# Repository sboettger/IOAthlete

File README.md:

# IOAthlete
A fork of the Reaction Training Dummy of instructables
https://www.instructables.com/Reaction-Training-Dummy/

TODO: add symbols and footprints to the repository

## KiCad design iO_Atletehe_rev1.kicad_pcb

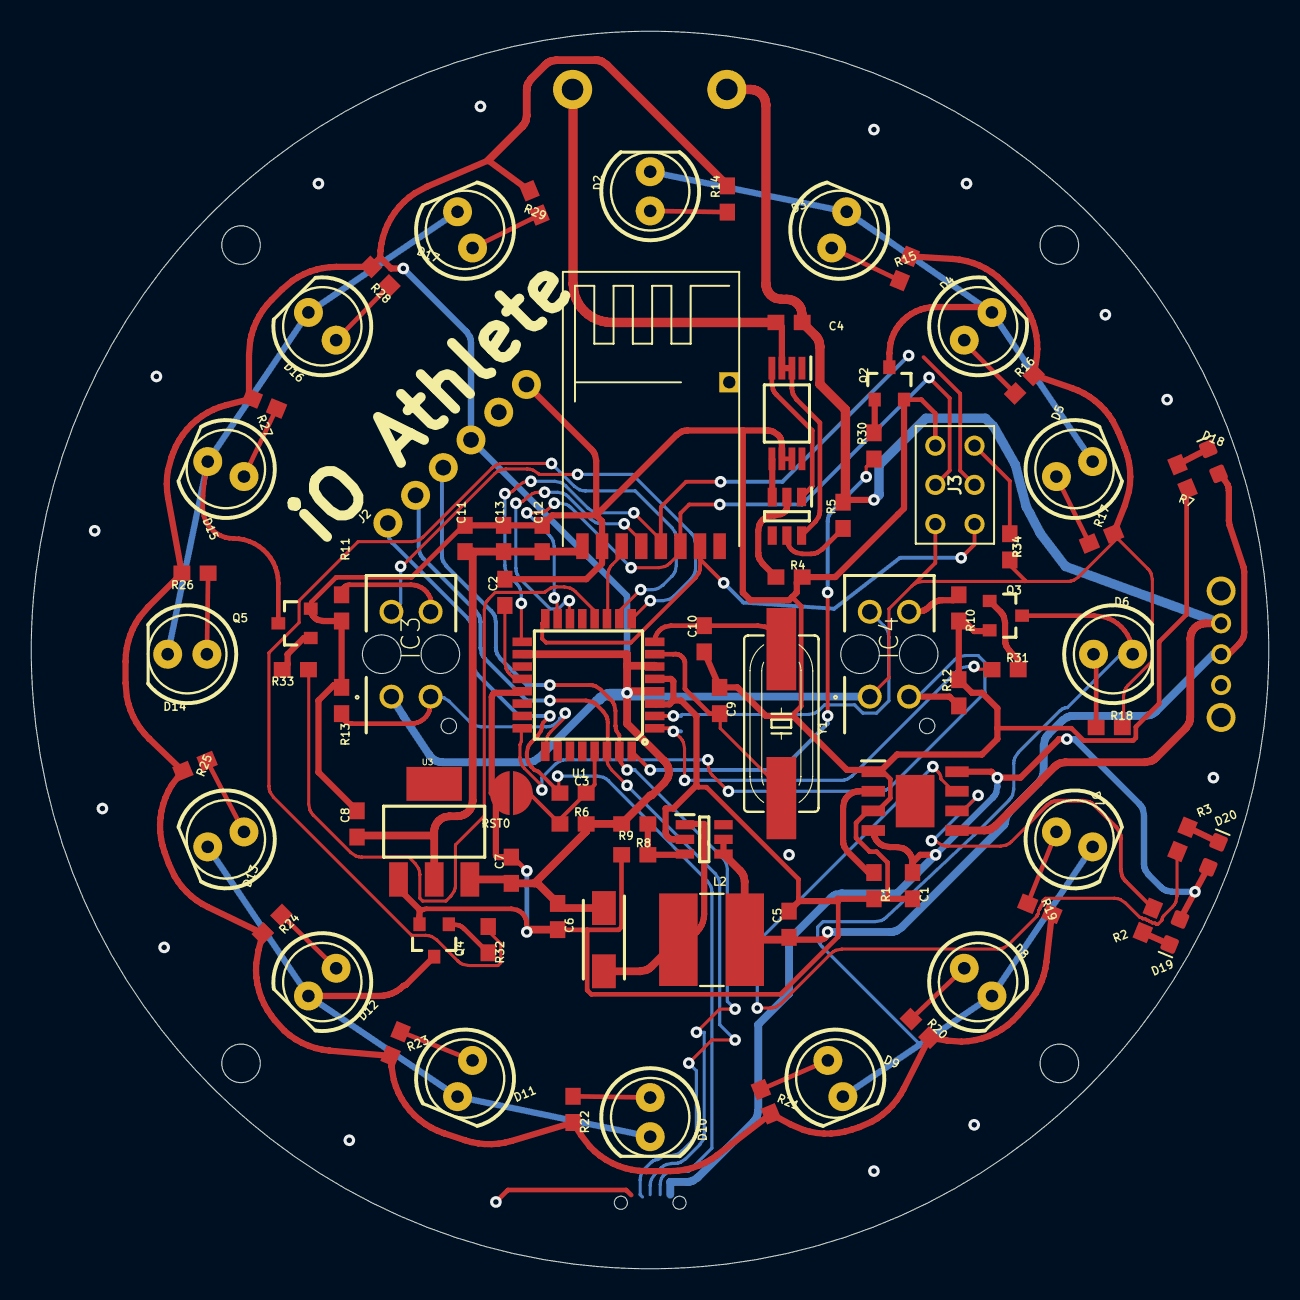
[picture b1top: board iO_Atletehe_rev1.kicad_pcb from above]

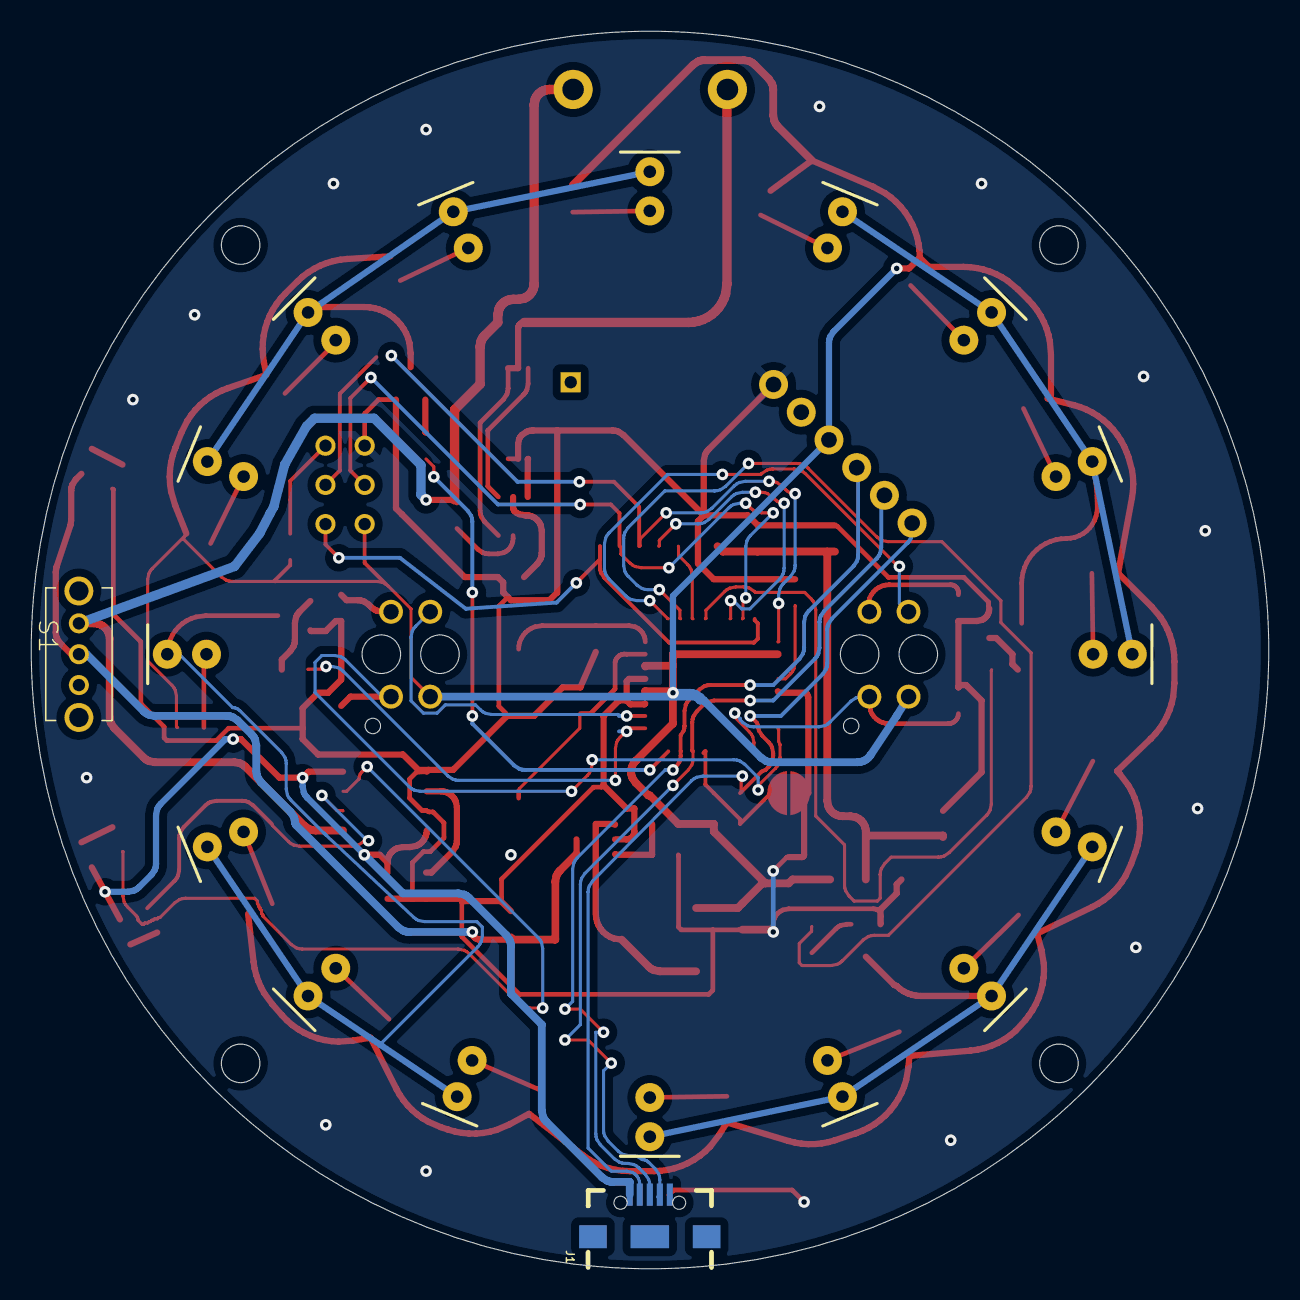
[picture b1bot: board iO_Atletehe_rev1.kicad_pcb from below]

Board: 2 copper layers, 80.2 x 80.2 mm, 92 parts (3 on the bottom side), 66 nets.

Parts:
@HOLE0, @HOLE1, @HOLE2, @HOLE3: (no value)
BT2: LIPO-1100MAH
C1, C7, C8, C11: 10uF; 0603
C2, C3, C4, C12, C13: 0.1uF; 0603
C5, C6: 22uF; 0603
C9, C10: 22pF; 0603
D1: SS14-E3_61T; DIOM5127X229N
D2, D3, D4, D5, D6, D7, D8, D9, D10, D11, D12, D13, D14, D15, D16, D17: LED_5MM
D18: Blue; LED-0603
D19: Green; LED-0603
D20: Red; LED-0603
IC1: TP4056; SOIC127P600X175-9N
IC2: FS312F-G; SOT95P280X145-6N
IC3, IC4: TCRT5000L
J1: USB-B-MICRO-SMD
J2: 1X06-KIT
J3: AVR-ISP
L2: 22µH/±20%/1.4A; SRN6045
Q1: FS8205A; SOP65P640X120-8N
Q2, Q3, Q4, Q5: 500mA/300V; SOT23-3
R1, R4: 2k; 0603
R2, R3, R7, R8, R30, R31, R32, R33: 1k; 0603
R5, R10, R11: 100; 0603
R6, R34: 10k; 0603
R9: 7.5k; 0603
R12, R13: 100k; 0603
R14, R15, R16, R17, R18, R19, R20, R21, R22, R23, R24, R25, R26, R27, R28, R29: 27; 0603
RST0: JUMPER-SMT_2_NO_NO-SILK_ROUND; SMT-JUMPER_2_NO_NO-SILK_ROUND
S1: SK12D07VG4NSPA
U1: ATMEGA328P_TQFP; TQFP32-08
U2: MT3608; SOT95P280X145-6N
U3: V_REG_LD1117V 3.3v; SOT223
U4: NRF24MINI
Y1: HC49UP

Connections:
3.3V: C8.1, C11.2, C12.2, C13.2, U3.2, U4.3V3
5V: C6.1, C7.1, D1.1, IC3.1, IC4.1, J2.4, J3.VCC, R6.2, R9.2, R14.2, R15.2, R16.2, R17.2, R18.2, R19.2, R20.2, R21.2, R22.2, R23.2, R24.2, R25.2, R26.2, R27.2, R28.2, R29.2, R34.2, U1.4, U1.6, U1.18, U3.3
/RESET: J3.RST, R34.1
A1: IC4.2, R12.1, U1.24
A2: IC3.2, R13.1, U1.25
AREF: C2.1, U1.20
D2: R30.1, U1.32
D3: R31.1, U1.1
D4: IC4.4, U1.2
D5: IC3.4, U1.9
D6: R32.1, U1.10
D7: U1.11, U4.CE
D8: R33.1, U1.12
D10: U1.14, U4.CSN
D11: J3.MOSI, U1.15, U4.MOSI
D12: J3.MISO, U1.16, U4.MISO
D13: J3.SCK, U1.17, U4.SCK
GND: C1.2, C2.2, C5.2, C6.2, C7.2, C8.2, C9.1, C10.1, C11.1, C12.1, C13.1, IC1.1, IC1.3, J1.GND, J2.6, J3.GND, Q1.6, Q1.7, Q2.2, Q3.2, Q4.2, Q5.2, R1.2, R4.2, R7.2, R8.1, R10.2, R11.1, R12.2, R13.2, RST0.2, U1.3, U1.5, U1.21, U2.2, U3.1, U4.GND
GND-ISO: BT2.-, C4.1, IC2.6, Q1.2, Q1.3
unnamed: IC2.3, Q1.5
unnamed: D18.C, R7.1
unnamed: IC1.2, R1.1
unnamed: D19.C, R2.1
unnamed: D20.C, R3.1
unnamed: IC1.6, R2.2
unnamed: IC1.7, R3.2
unnamed: IC2.2, R4.1
unnamed: IC2.5, R5.1
unnamed: C9.2, U1.7, Y1.2
unnamed: C10.2, U1.8, Y1.1
unnamed: D1.2, L2.1, U2.1
unnamed: R8.2, R9.1, U2.3
unnamed: C5.1, D18.A, L2.2, S1.2, U2.4, U2.5
unnamed: IC4.3, R10.1
unnamed: D2.A, R14.1
unnamed: IC3.3, R11.2
unnamed: D3.A, R15.1
unnamed: D4.A, R16.1
unnamed: D5.A, R17.1
unnamed: D6.A, R18.1
unnamed: D7.A, R19.1
unnamed: D8.A, R20.1
unnamed: D9.A, R21.1
unnamed: D10.A, R22.1
unnamed: D11.A, R23.1
unnamed: D14.A, R26.1
unnamed: D13.A, R25.1
unnamed: D12.A, R24.1
unnamed: D15.A, R27.1
unnamed: D16.A, R28.1
unnamed: D17.A, R29.1
unnamed: D2.K, D3.K, D4.K, D5.K, Q2.3
unnamed: D6.K, D7.K, D8.K, D9.K, Q3.3
unnamed: D10.K, D11.K, D12.K, D13.K, Q4.3
unnamed: D14.K, D15.K, D16.K, D17.K, Q5.3
unnamed: Q2.1, R30.2
unnamed: Q3.1, R31.2
unnamed: Q4.1, R32.2
unnamed: Q5.1, R33.2
OD: IC2.1, Q1.4
RESET: C3.2, R6.1, RST0.1, U1.29
RESET_CAP: C3.1, J1.D-, J2.1
RXD: J1.ID, J2.2, U1.30
TXD: J1.D+, J2.3, U1.31
VIN: C1.1, D19.A, D20.A, IC1.4, IC1.8, J1.VBUS
V_BATT: BT2.+, C4.2, IC1.5, R5.2, S1.1

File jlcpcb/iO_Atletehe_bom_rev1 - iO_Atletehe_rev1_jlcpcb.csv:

,,,
Designator,Value,LCSC part number,Footprint
D18,Blue,C84266,LED-0603
D19,Green,C205443,LED-0603
D20,Red,C84263,LED-0603
BT2,BATTERY1100,,LIPO-1100MAH
"C1, C7, C8, C11",10uF,C1691,0603
"C2, C3, C4, C12, C13",0.1uF,C30926,0603
"C5, C6",22uF,C159801,0603
"C9, C10",22pF,C1653,0603
D1,SS14-E3_61T,C2480,DIOM5127X229N
"D2, D3, D4, D5, D6, D7, D8, D9, D10, D11, D12, D13, D14, D15, D16, D17",LED5MM,,LED_5MM
IC1,TP4056,C16581,SOIC127P600X175-9N
IC2,FS312F-G,C82736,SOT95P280X145-6N
"IC3, IC4",TCRT5000L,,TCRT5000L
J1,USB_MICRO-B_FEMALE-SMT,,USB-B-MICRO-SMD
J2,6_PIN_SERIAL_TARGETPTH-KIT,,1X06-KIT
J3,AVR-ISP-6,,kicad_footprints_sb:AVR-ISP-6
L2,22µH/±20%/1.4A,C9391,SRN6045
Q1,FS8205A,C16052,SOP65P640X120-8N
"Q2, Q3, Q4, Q5",500mA/300V,C2150,SOT23-3
"R1, R4",2k,C25590,0603
"R2, R3, R7, R8",1k,C21190,0603
"R5, R10, R11",100,C25201,0603
R6,10k,C25804,0603
R9,7.5k,C103813,0603
"R12, R13",100k,C15458,0603
"R14, R15, R16, R17, R18, R19, R20, R21, R22, R23, R24, R25, R26, R27, R28, R29",27,C137753,0603
"R30, R31, R32, R33",1k,C21190,0603
R34,10k,C25804,0603
RST0,JUMPER-SMT_2_NO_NO-SILK_ROUND,,SMT-JUMPER_2_NO_NO-SILK_ROUND
S1,SK12D07VG4NSPA,C131374,SK12D07VG4NSPA
U1,ATMEGA328P_TQFP,C14877,TQFP32-08
U2,MT3608,C84817,SOT95P280X145-6N
U3,V_REG_LD1117V 3.3v,C126027,SOT223
U4,NRF24MINI,,NRF24MINI
Y1,CRYSTALSMD-HC49UP,C259047,HC49UP

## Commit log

2022-11-19 Update README.md
    added link to original instructable
